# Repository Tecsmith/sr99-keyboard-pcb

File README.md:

# SR99-Keyboard-PCB

> :warning: **WIP:** Work in Progress design, and is not tested.  Please hold-off on building until the design can be verified and the software is written.

## Intent

A 980-layout (99-key) compact near-full size keyboard.

## Progression

> :bangbang: This is a "when I'm bored" project - so "significant" progress is not expected.

- **12 Jun 2026**
  - KiCAD 10 re-do done, but not built
- **15 Nov 2025**: Re-do begins!
  - EAGLE design abandoned in favour of KiCAD design
  - `STM32F411` discarded for **`STM32G474`**
- ~~**27 Sep 2024**: Beta 1 done~~
  - ~~:warning: Not manufactured~~
  - ~~:warning: Not tested~~
- See [CHANGELOG.md](CHANGELOG.md)

<!--
### Resources

 - Schematic PDF [here](docs/sr99-revXXX.pdf)
 - EAGLE BRD *(PCB)* [here](EAGLE/sr99/sr99-revXXX.brd)
 - EAGLE SCH *(Schematic)* [here](EAGLE/sr99/sr99-revXXX.sch)
-->

### Beta PCB renders

#### Top

#### Bottom *(Component side)*

◊
### Layout ideation renders

#### Render

#### Layout

#### Matrix coordinates *(QMK & VIA)*

## Planned Features

- [ ] QMK build, with Via/l support
- [x] 1x `STM32G474` STM32 CPU *(based on Black Pill design)*
- [x] 1x `M95640-DRE` 8K SPI EEPROM Module
- [x] 3x `MC74HC589A` SPI Input Shift Registers *- possibly faster scan rates*
- [x] 2x `IS31FL3743B` RGB Drivers, with independent LDOs
- [ ] 2x SKYLOONG rotary encoder/switch positions
- [x] UDB C-Series Usb-C JST-SH

<!--
#### Addons / Wishlist

- [ ] DIP Switch daughter board *(4-position)*
- [ ] ~~Case slide switch daughter board *(Win/Mac 2-state, + USB+BT+2.4GHz 3-state)*~~ *(To do)*
- [ ] USB 2.0 Hub
-->

<!--
## Wishlist

- [ ] Drop in replacement PCB *(e.g. compatible standoff positions)* for:
    - Brutal v2 1800
    - Monsgeek M2
    - ~~Skyloong GK980~~ *(The GK980 has a 0.5U gap between Esc and F1, making it not the same footprint as the B1k8 and M2.)*
-->

---

Made with :heart: by [**Silvino R**](https://github.com/silvinor)

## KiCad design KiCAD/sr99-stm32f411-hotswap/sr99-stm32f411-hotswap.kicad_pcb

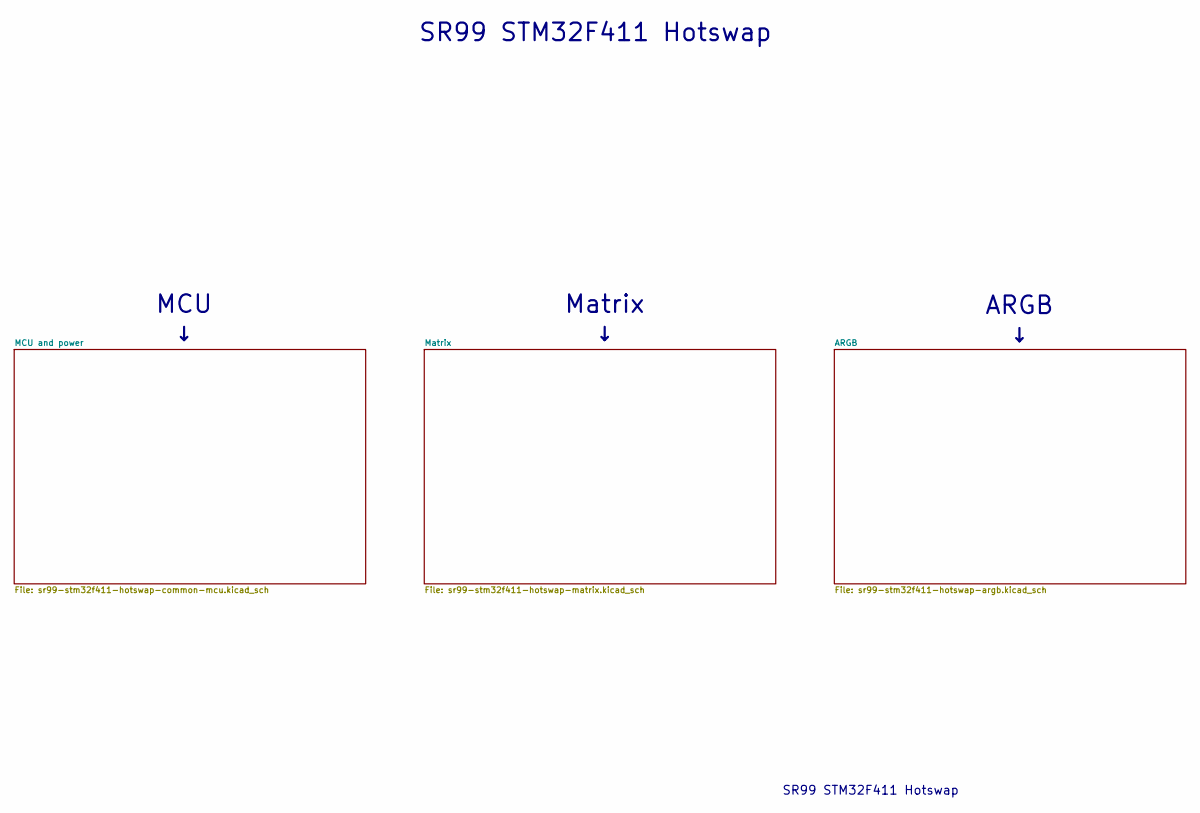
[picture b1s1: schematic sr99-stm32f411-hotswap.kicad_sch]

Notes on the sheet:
ARGB ↓
MCU ↓
SR99 STM32F411 Hotswap
Matrix ↓

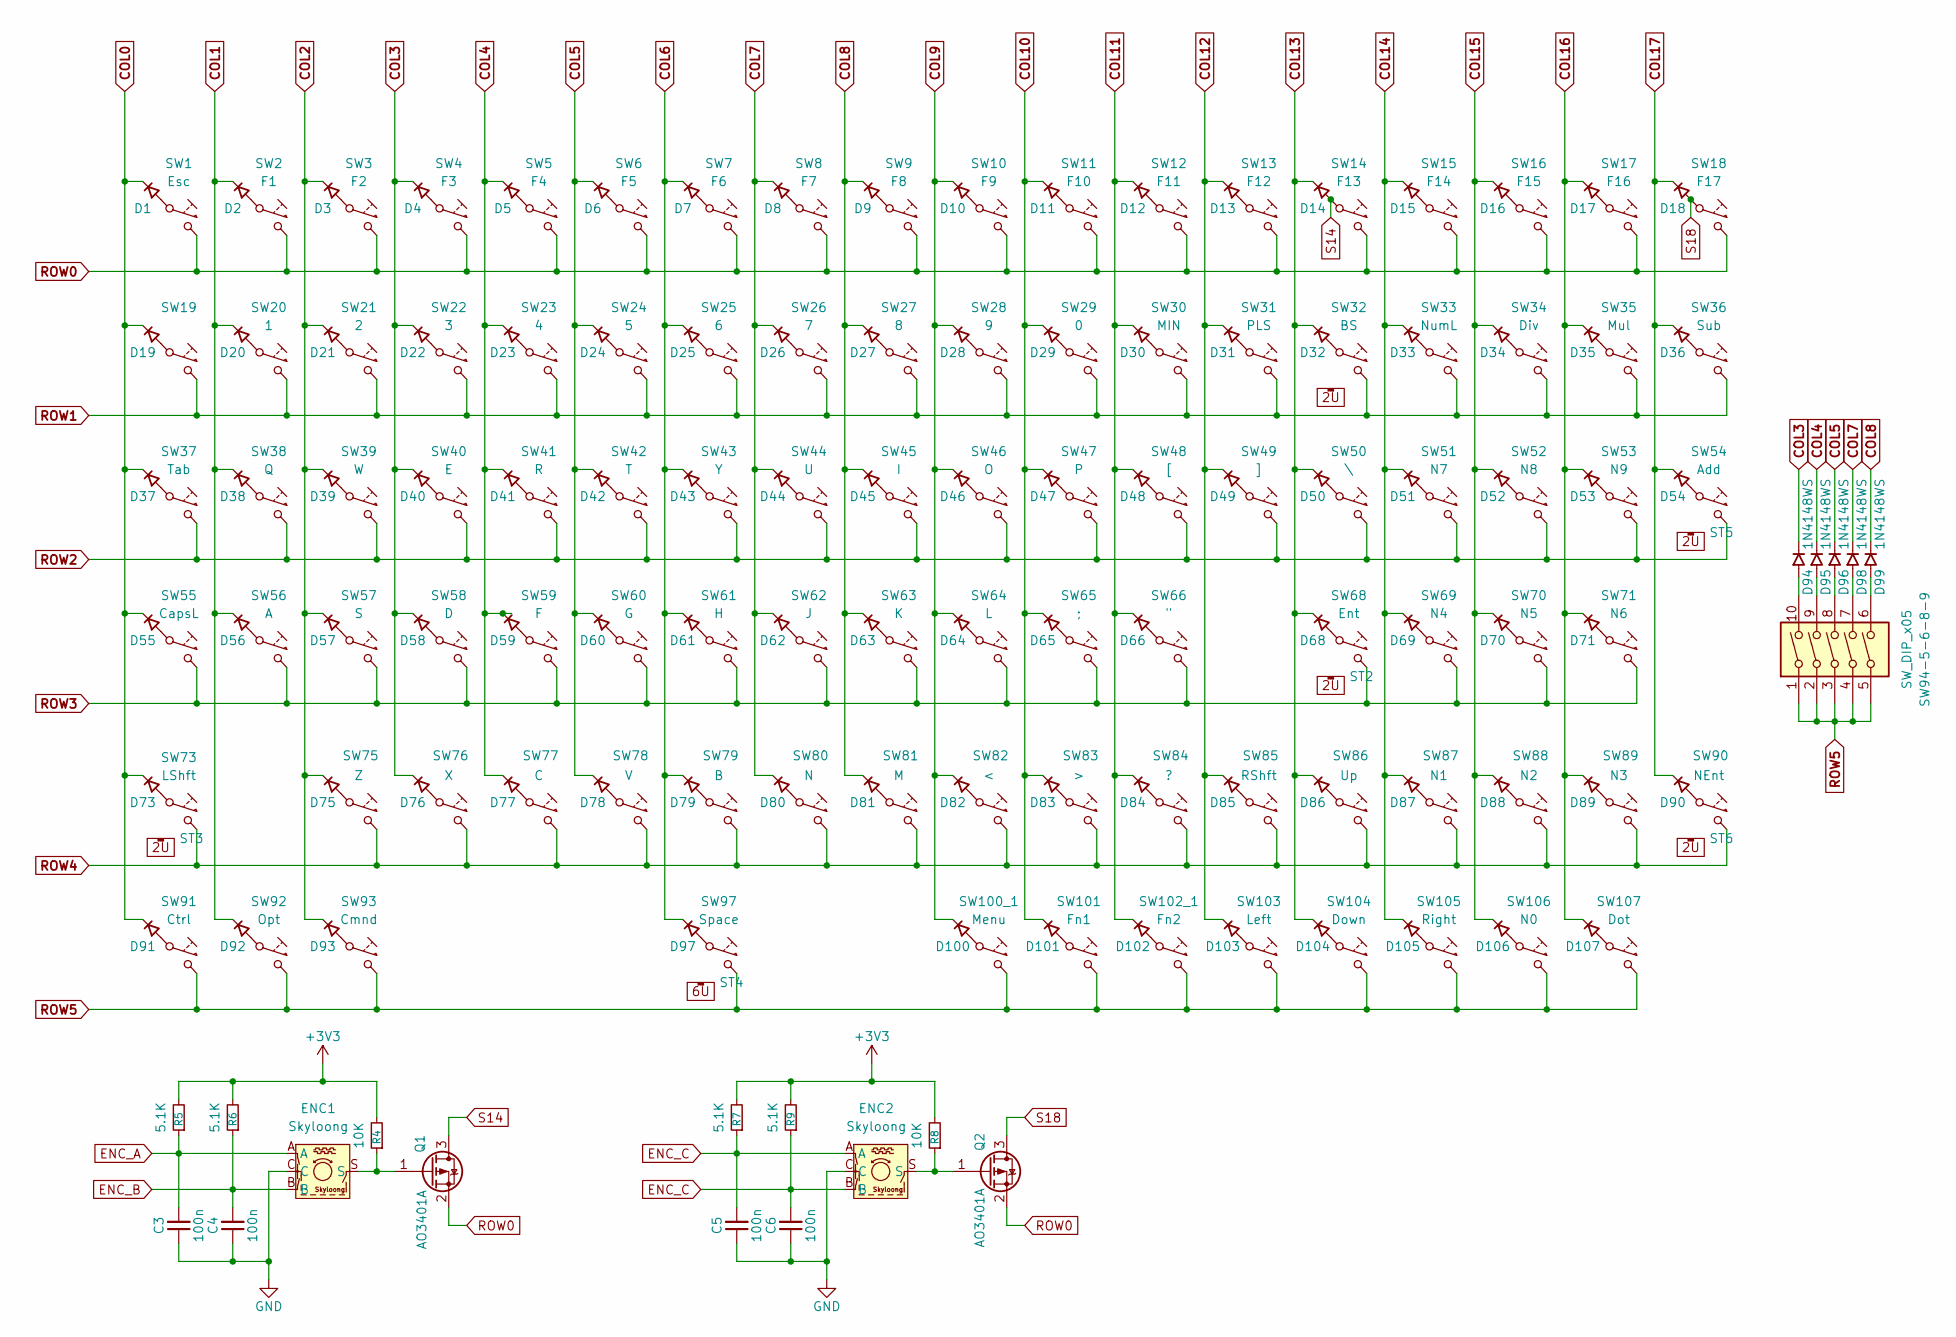
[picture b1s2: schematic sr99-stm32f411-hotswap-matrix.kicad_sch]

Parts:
C3, C4, C5, C6: 100n; C_0603_1608Metric_Pad1.08x0.95mm_HandSolder
D1, D2, D3, D4, D5, D6, D7, D8, D9, D10, D11, D12, D13, D14, D15, D16, D17, D18, D19, D20, D21, D22, D23, D24, D25, D26, D27, D28, D29, D30, D31, D32, D33, D34, D35, D36, D37, D38, D39, D40, D41, D42, D43, D44, D45, D46, D47, D48, D49, D50, D51, D52, D53, D54, D55, D56, D57, D58, D59, D60, D61, D62, D63, D64, D65, D66, D68, D69, D70, D71, D73, D75, D76, D77, D78, D79, D80, D81, D82, D83, D84, D85, D86, D87, D88, D89, D90, D91, D92, D93, D97, D100, D101, D102, D103, D104, D105, D106, D107: 1N4148WS; D_SOD-323_HandSoldering
D94, D95, D96, D98, D99: 1N4148WS
ENC1, ENC2: Skyloong; SW_Skyloong_Enc
Q1, Q2: AO3401A; SOT-23
R4, R8: 10K; R_0603_1608Metric_Pad0.98x0.95mm_HandSolder
R5, R6, R7, R9: 5.1K; R_0603_1608Metric_Pad0.98x0.95mm_HandSolder
ST1, ST2, ST3, ST5, ST6: STAB_2U
ST4: STAB_6U
SW1: Esc; SW_MX_HotSwap
SW2: F1; SW_MX_HotSwap
SW3: F2; SW_MX_HotSwap
SW4: F3; SW_MX_HotSwap
SW5: F4; SW_MX_HotSwap
SW6: F5; SW_MX_HotSwap
SW7: F6; SW_MX_HotSwap
SW8: F7; SW_MX_HotSwap
SW9: F8; SW_MX_HotSwap
SW10: F9; SW_MX_HotSwap
SW11: F10; SW_MX_HotSwap
SW12: F11; SW_MX_HotSwap
SW13: F12; SW_MX_HotSwap
SW14: F13; SW_MX_HotSwap
SW15: F14; SW_MX_HotSwap
SW16: F15; SW_MX_HotSwap
SW17: F16; SW_MX_HotSwap
SW18: F17; SW_MX_HotSwap
SW19: SW_MX_HotSwap
SW20: 1; SW_MX_HotSwap
SW21: 2; SW_MX_HotSwap
SW22: 3; SW_MX_HotSwap
SW23: 4; SW_MX_HotSwap
SW24: 5; SW_MX_HotSwap
SW25: 6; SW_MX_HotSwap
SW26: 7; SW_MX_HotSwap
SW27: 8; SW_MX_HotSwap
SW28: 9; SW_MX_HotSwap
SW29: 0; SW_MX_HotSwap
SW30: MIN; SW_MX_HotSwap
SW31: PLS; SW_MX_HotSwap
SW32: BS; SW_MX_HotSwap
SW33: NumL; SW_MX_HotSwap
SW34: Div; SW_MX_HotSwap
SW35: Mul; SW_MX_HotSwap
SW36: Sub; SW_MX_HotSwap
SW37: Tab; SW_MX_HotSwap
SW38: Q; SW_MX_HotSwap
SW39: W; SW_MX_HotSwap
SW40: E; SW_MX_HotSwap
SW41: R; SW_MX_HotSwap
SW42: T; SW_MX_HotSwap
SW43: Y; SW_MX_HotSwap
SW44: U; SW_MX_HotSwap
SW45: I; SW_MX_HotSwap
SW46: O; SW_MX_HotSwap
SW47: P; SW_MX_HotSwap
SW48: [; SW_MX_HotSwap
SW49: ]; SW_MX_HotSwap
SW50: \; SW_MX_HotSwap
SW51: N7; SW_MX_HotSwap
SW52: N8; SW_MX_HotSwap
SW53: N9; SW_MX_HotSwap
SW54: Add; SW_MX_HotSwap
SW55: CapsL; SW_MX_HotSwap
SW56: A; SW_MX_HotSwap
SW57: S; SW_MX_HotSwap
SW58: D; SW_MX_HotSwap
SW59: F; SW_MX_HotSwap
SW60: G; SW_MX_HotSwap
SW61: H; SW_MX_HotSwap
SW62: J; SW_MX_HotSwap
SW63: K; SW_MX_HotSwap
SW64: L; SW_MX_HotSwap
SW65: ;; SW_MX_HotSwap
SW66: "; SW_MX_HotSwap
SW68: Ent; SW_MX_HotSwap
SW69: N4; SW_MX_HotSwap
SW70: N5; SW_MX_HotSwap
SW71: N6; SW_MX_HotSwap
SW73: LShft; SW_MX_HotSwap
SW75: Z; SW_MX_HotSwap
SW76: X; SW_MX_HotSwap
SW77: C; SW_MX_HotSwap
SW78: V; SW_MX_HotSwap
SW79: B; SW_MX_HotSwap
SW80: N; SW_MX_HotSwap
SW81: M; SW_MX_HotSwap
SW82: <; SW_MX_HotSwap
SW83: >; SW_MX_HotSwap
SW84: ?; SW_MX_HotSwap
SW85: RShft; SW_MX_HotSwap
SW86: Up; SW_MX_HotSwap
SW87: N1; SW_MX_HotSwap
SW88: N2; SW_MX_HotSwap
SW89: N3; SW_MX_HotSwap
SW90: NEnt; SW_MX_HotSwap
SW91: Ctrl; SW_MX_HotSwap
SW92: Opt; SW_MX_HotSwap
SW93: Cmnd; SW_MX_HotSwap
SW94-5-6-8-9: SW_DIP_x05
SW97: Space; SW_MX_HotSwap
SW100_1: Menu; SW_MX_HotSwap
SW101: Fn1; SW_MX_HotSwap
SW102_1: Fn2; SW_MX_HotSwap
SW103: Left; SW_MX_HotSwap
SW104: Down; SW_MX_HotSwap
SW105: Right; SW_MX_HotSwap
SW106: N0; SW_MX_HotSwap
SW107: Dot; SW_MX_HotSwap

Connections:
+3V3: R4.2, R5.2, R6.2, R7.2, R8.2, R9.2
COL0: D1.1 (K), D19.1 (K), D37.1 (K), D55.1 (K), D73.1 (K), D91.1 (K)
COL1: D2.1 (K), D20.1 (K), D38.1 (K), D56.1 (K), D92.1 (K)
COL2: D3.1 (K), D21.1 (K), D39.1 (K), D57.1 (K), D75.1 (K), D93.1 (K)
COL3: D4.1 (K), D22.1 (K), D40.1 (K), D58.1 (K), D76.1 (K), D94.1 (K)
COL4: D5.1 (K), D23.1 (K), D41.1 (K), D59.1 (K), D77.1 (K), D95.1 (K)
COL5: D6.1 (K), D24.1 (K), D42.1 (K), D60.1 (K), D78.1 (K), D96.1 (K)
COL6: D7.1 (K), D25.1 (K), D43.1 (K), D61.1 (K), D79.1 (K), D97.1 (K)
COL7: D8.1 (K), D26.1 (K), D44.1 (K), D62.1 (K), D80.1 (K), D98.1 (K)
COL8: D9.1 (K), D27.1 (K), D45.1 (K), D63.1 (K), D81.1 (K), D99.1 (K)
COL9: D10.1 (K), D28.1 (K), D46.1 (K), D64.1 (K), D82.1 (K), D100.1 (K)
COL10: D11.1 (K), D29.1 (K), D47.1 (K), D65.1 (K), D83.1 (K), D101.1 (K)
COL11: D12.1 (K), D30.1 (K), D48.1 (K), D66.1 (K), D84.1 (K), D102.1 (K)
COL12: D13.1 (K), D31.1 (K), D49.1 (K), D85.1 (K), D103.1 (K)
COL13: D14.1 (K), D32.1 (K), D50.1 (K), D68.1 (K), D86.1 (K), D104.1 (K)
COL14: D15.1 (K), D33.1 (K), D51.1 (K), D69.1 (K), D87.1 (K), D105.1 (K)
COL15: D16.1 (K), D34.1 (K), D52.1 (K), D70.1 (K), D88.1 (K), D106.1 (K)
COL16: D17.1 (K), D35.1 (K), D53.1 (K), D71.1 (K), D89.1 (K), D107.1 (K)
COL17: D18.1 (K), D36.1 (K), D54.1 (K), D90.1 (K)
ENC_A: C3.2, ENC1.A, R5.1
ENC_B: C4.2, ENC1.B, R6.1
ENC_C: C5.2, C6.2, ENC2.A, ENC2.B, R7.1, R9.1
GND: C3.1, C4.1, C5.1, C6.1, ENC1.C, ENC2.C; also elsewhere on the board
unnamed: D1.2 (A), SW1.1
unnamed: D2.2 (A), SW2.1
unnamed: D3.2 (A), SW3.1
unnamed: D4.2 (A), SW4.1
unnamed: D5.2 (A), SW5.1
unnamed: D6.2 (A), SW6.1
unnamed: D7.2 (A), SW7.1
unnamed: D8.2 (A), SW8.1
unnamed: D9.2 (A), SW9.1
unnamed: D10.2 (A), SW10.1
unnamed: D11.2 (A), SW11.1
unnamed: D12.2 (A), SW12.1
unnamed: D13.2 (A), SW13.1
unnamed: D15.2 (A), SW15.1
unnamed: D16.2 (A), SW16.1
unnamed: D17.2 (A), SW17.1
unnamed: D19.2 (A), SW19.1
unnamed: D20.2 (A), SW20.1
unnamed: D21.2 (A), SW21.1
unnamed: D22.2 (A), SW22.1
unnamed: D23.2 (A), SW23.1
unnamed: D24.2 (A), SW24.1
unnamed: D25.2 (A), SW25.1
unnamed: D26.2 (A), SW26.1
unnamed: D27.2 (A), SW27.1
unnamed: D28.2 (A), SW28.1
unnamed: D29.2 (A), SW29.1
unnamed: D30.2 (A), SW30.1
unnamed: D31.2 (A), SW31.1
unnamed: D32.2 (A), SW32.1
unnamed: D33.2 (A), SW33.1
unnamed: D34.2 (A), SW34.1
unnamed: D35.2 (A), SW35.1
unnamed: D36.2 (A), SW36.1
unnamed: D37.2 (A), SW37.1
unnamed: D38.2 (A), SW38.1
unnamed: D39.2 (A), SW39.1
unnamed: D40.2 (A), SW40.1
unnamed: D41.2 (A), SW41.1
unnamed: D42.2 (A), SW42.1
unnamed: D43.2 (A), SW43.1
unnamed: D44.2 (A), SW44.1
unnamed: D45.2 (A), SW45.1
unnamed: D46.2 (A), SW46.1
unnamed: D47.2 (A), SW47.1
unnamed: D48.2 (A), SW48.1
unnamed: D49.2 (A), SW49.1
unnamed: D50.2 (A), SW50.1
unnamed: D51.2 (A), SW51.1
unnamed: D52.2 (A), SW52.1
unnamed: D53.2 (A), SW53.1
unnamed: D54.2 (A), SW54.1
unnamed: D55.2 (A), SW55.1
unnamed: D56.2 (A), SW56.1
unnamed: D57.2 (A), SW57.1
unnamed: D58.2 (A), SW58.1
unnamed: D59.2 (A), SW59.1
unnamed: D60.2 (A), SW60.1
unnamed: D61.2 (A), SW61.1
unnamed: D62.2 (A), SW62.1
unnamed: D63.2 (A), SW63.1
unnamed: D64.2 (A), SW64.1
unnamed: D65.2 (A), SW65.1
unnamed: D66.2 (A), SW66.1
unnamed: D68.2 (A), SW68.1
unnamed: D69.2 (A), SW69.1
unnamed: D70.2 (A), SW70.1
unnamed: D71.2 (A), SW71.1
unnamed: D73.2 (A), SW73.1
unnamed: D75.2 (A), SW75.1
unnamed: D76.2 (A), SW76.1
unnamed: D77.2 (A), SW77.1
unnamed: D78.2 (A), SW78.1
unnamed: D79.2 (A), SW79.1
unnamed: D80.2 (A), SW80.1
unnamed: D81.2 (A), SW81.1
unnamed: D82.2 (A), SW82.1
unnamed: D83.2 (A), SW83.1
unnamed: D84.2 (A), SW84.1
unnamed: D85.2 (A), SW85.1
unnamed: D86.2 (A), SW86.1
unnamed: D87.2 (A), SW87.1
unnamed: D88.2 (A), SW88.1
unnamed: D89.2 (A), SW89.1
unnamed: D90.2 (A), SW90.1
unnamed: D91.2 (A), SW91.1
unnamed: D92.2 (A), SW92.1
unnamed: D93.2 (A), SW93.1
unnamed: D94.2 (A), SW94-5-6-8-9.10
unnamed: D95.2 (A), SW94-5-6-8-9.9
unnamed: D96.2 (A), SW94-5-6-8-9.8
unnamed: D97.2 (A), SW97.1
unnamed: D98.2 (A), SW94-5-6-8-9.7
unnamed: D99.2 (A), SW94-5-6-8-9.6
unnamed: D100.2 (A), SW100_1.1
unnamed: D101.2 (A), SW101.1
unnamed: D102.2 (A), SW102_1.1
unnamed: D103.2 (A), SW103.1
unnamed: D104.2 (A), SW104.1
unnamed: D105.2 (A), SW105.1
unnamed: D106.2 (A), SW106.1
unnamed: D107.2 (A), SW107.1
unnamed: ENC1.S, Q1.1 (G), R4.1
unnamed: ENC2.S, Q2.1 (G), R8.1
ROW0: Q1.2 (S), Q2.2 (S), SW1.2, SW2.2, SW3.2, SW4.2, SW5.2, SW6.2, SW7.2, SW8.2, SW9.2, SW10.2, SW11.2, SW12.2, SW13.2, SW14.2, SW15.2, SW16.2, SW17.2, SW18.2
ROW1: SW19.2, SW20.2, SW21.2, SW22.2, SW23.2, SW24.2, SW25.2, SW26.2, SW27.2, SW28.2, SW29.2, SW30.2, SW31.2, SW32.2, SW33.2, SW34.2, SW35.2, SW36.2
ROW2: SW37.2, SW38.2, SW39.2, SW40.2, SW41.2, SW42.2, SW43.2, SW44.2, SW45.2, SW46.2, SW47.2, SW48.2, SW49.2, SW50.2, SW51.2, SW52.2, SW53.2, SW54.2
ROW3: SW55.2, SW56.2, SW57.2, SW58.2, SW59.2, SW60.2, SW61.2, SW62.2, SW63.2, SW64.2, SW65.2, SW66.2, SW68.2, SW69.2, SW70.2, SW71.2
ROW4: SW73.2, SW75.2, SW76.2, SW77.2, SW78.2, SW79.2, SW80.2, SW81.2, SW82.2, SW83.2, SW84.2, SW85.2, SW86.2, SW87.2, SW88.2, SW89.2, SW90.2
ROW5: SW91.2, SW92.2, SW93.2, SW94-5-6-8-9.1, SW94-5-6-8-9.2, SW94-5-6-8-9.3, SW94-5-6-8-9.4, SW94-5-6-8-9.5, SW97.2, SW100_1.2, SW101.2, SW102_1.2, SW103.2, SW104.2, SW105.2, SW106.2, SW107.2
S14: D14.2 (A), Q1.3 (D), SW14.1
S18: D18.2 (A), Q2.3 (D), SW18.1

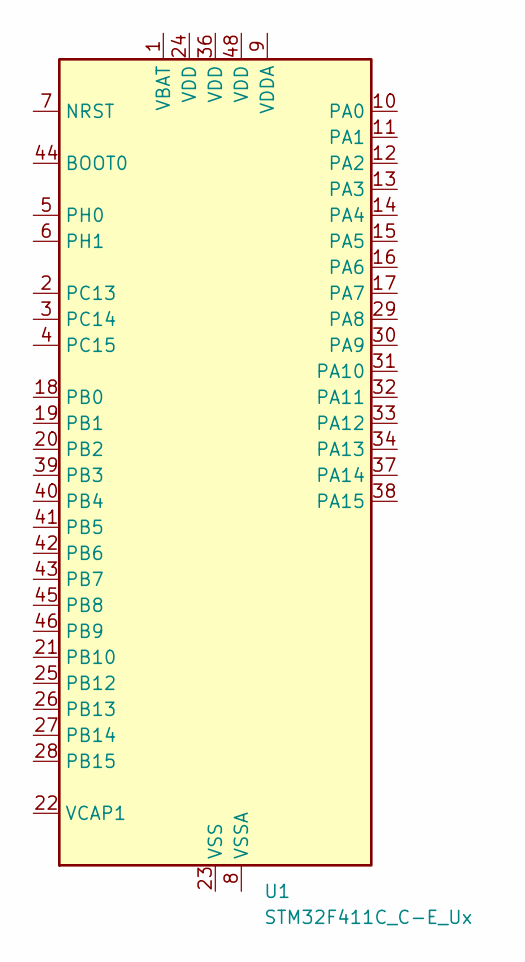
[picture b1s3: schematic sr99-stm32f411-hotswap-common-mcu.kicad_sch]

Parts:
U1: STM32F411C_C-E_Ux; QFN-48-1EP_7x7mm_P0.5mm_EP5.6x5.6mm

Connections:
unnamed: U1.23 (VSS), U1.35 (VSS), U1.47 (VSS), U1.49 (VSS)

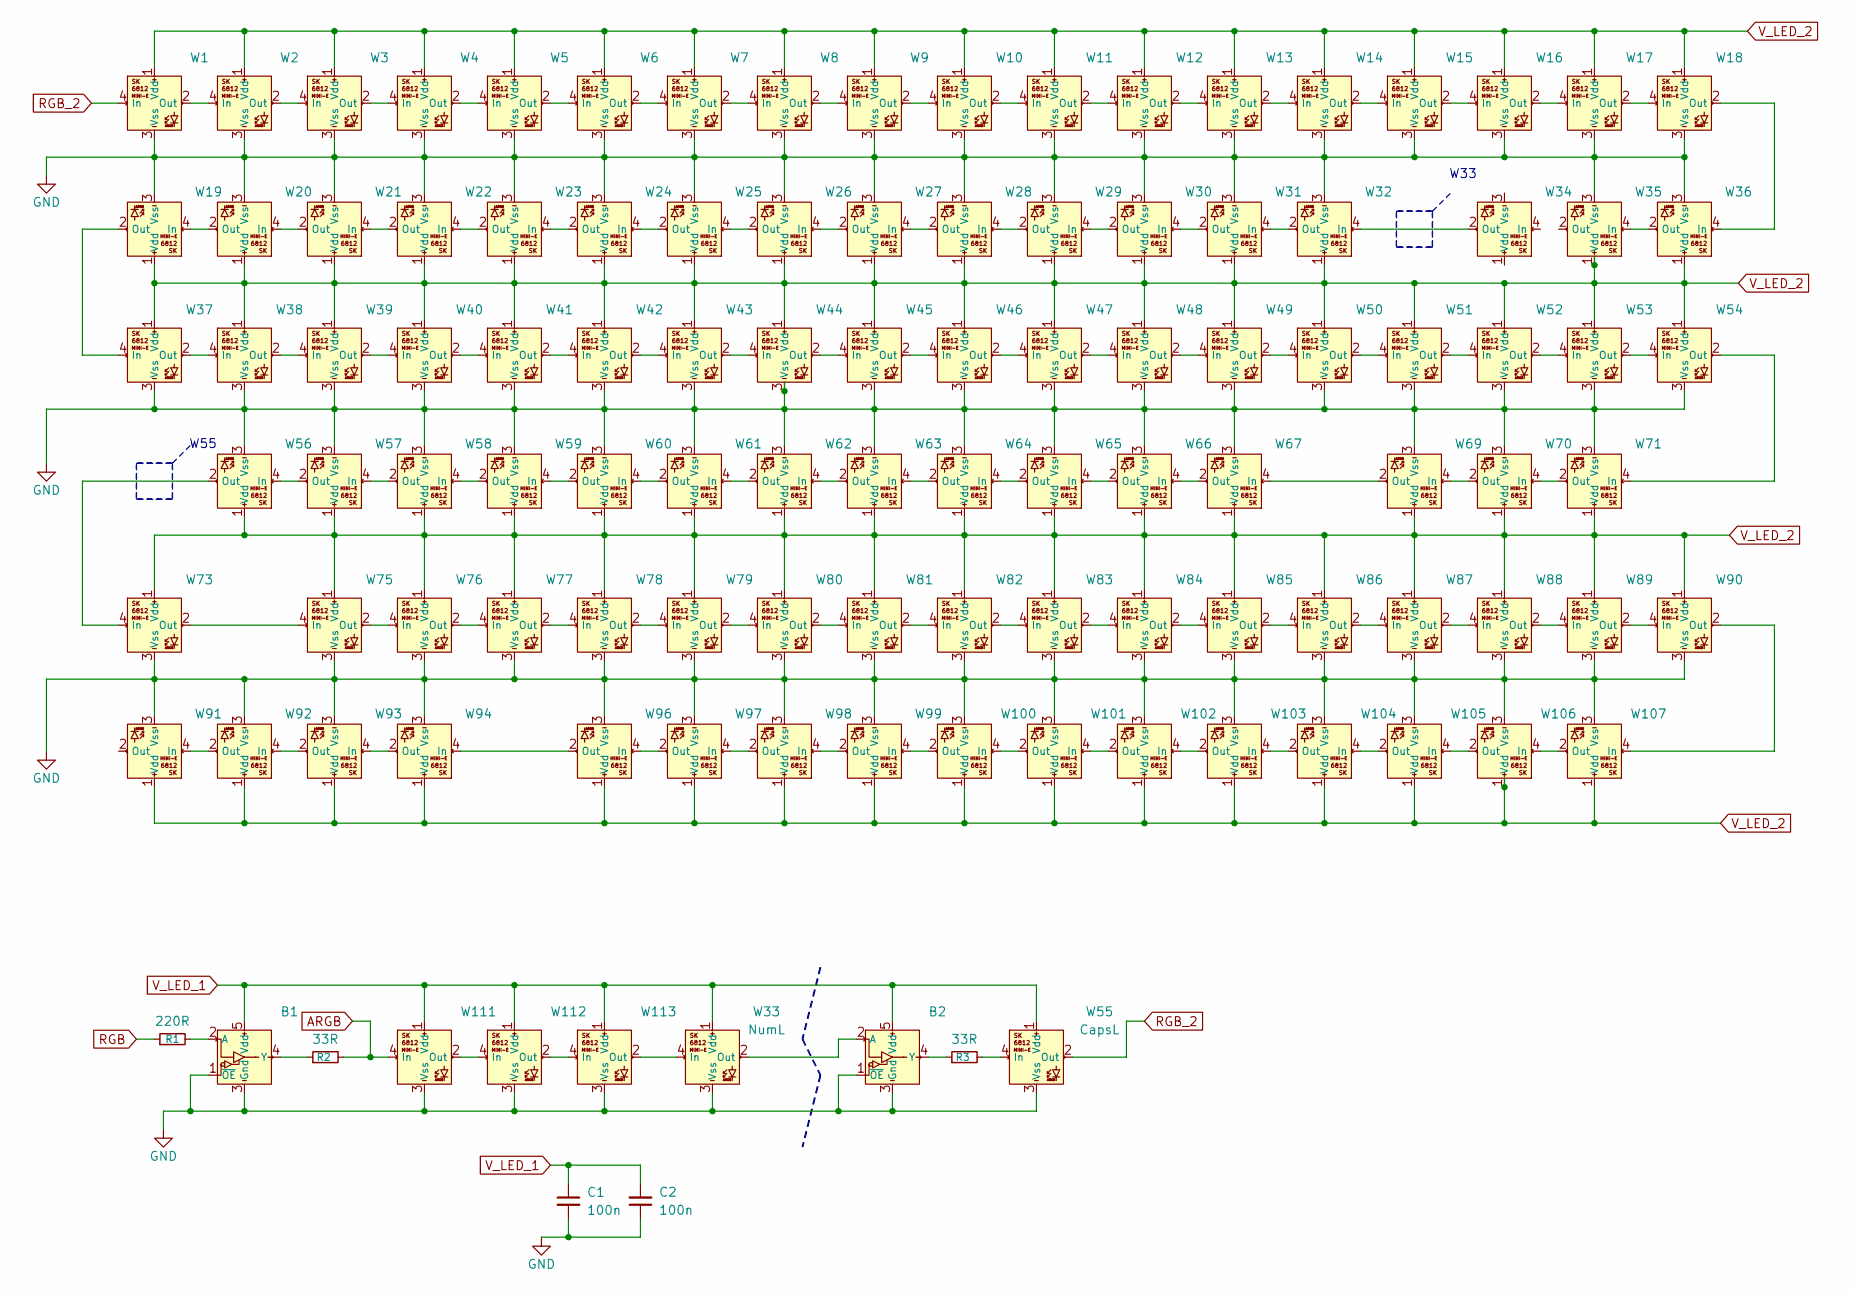
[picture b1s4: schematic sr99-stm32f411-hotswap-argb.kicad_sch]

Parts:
B1, B2: SOT-23-5
C1, C2: 100n; C_0603_1608Metric_Pad1.08x0.95mm_HandSolder
R1: 220R; R_0603_1608Metric_Pad0.98x0.95mm_HandSolder
R2, R3: 33R; R_0603_1608Metric_Pad0.98x0.95mm_HandSolder
W1, W2, W3, W4, W5, W6, W7, W8, W9, W10, W11, W12, W13, W14, W15, W16, W17, W18, W19, W20, W21, W22, W23, W24, W25, W26, W27, W28, W29, W30, W31, W32, W34, W35, W36, W37, W38, W39, W40, W41, W42, W43, W44, W45, W46, W47, W48, W49, W50, W51, W52, W53, W54, W56, W57, W58, W59, W60, W61, W62, W63, W64, W65, W66, W67, W69, W70, W71, W73, W75, W76, W77, W78, W79, W80, W81, W82, W83, W84, W85, W86, W87, W88, W89, W90, W91, W92, W93, W94, W96, W97, W98, W99, W100, W101, W102, W103, W104, W105, W106, W107, W111, W112, W113: SK6812MINI-E
W33: NumL; SK6812MINI-E
W55: CapsL; SK6812MINI-E

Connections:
ARGB: R2.2, W111.4 (In)
GND: B1.1 (~OE), B1.3 (Gnd), B2.1 (~OE), B2.3 (Gnd), C1.2, C2.1, W1.3 (Vss), W2.3 (Vss), W3.3 (Vss), W4.3 (Vss), W5.3 (Vss), W6.3 (Vss), W7.3 (Vss), W8.3 (Vss), W9.3 (Vss), W10.3 (Vss), W11.3 (Vss), W12.3 (Vss), W13.3 (Vss), W14.3 (Vss), W15.3 (Vss), W16.3 (Vss), W17.3 (Vss), W18.3 (Vss), W19.3 (Vss), W20.3 (Vss), W21.3 (Vss), W22.3 (Vss), W23.3 (Vss), W24.3 (Vss), W25.3 (Vss), W26.3 (Vss), W27.3 (Vss), W28.3 (Vss), W29.3 (Vss), W30.3 (Vss), W31.3 (Vss), W32.3 (Vss), W33.3 (Vss), W35.3 (Vss), W36.3 (Vss), W37.3 (Vss), W38.3 (Vss), W39.3 (Vss), W40.3 (Vss), W41.3 (Vss), W42.3 (Vss), W43.3 (Vss), W44.3 (Vss), W45.3 (Vss), W46.3 (Vss), W47.3 (Vss), W48.3 (Vss), W49.3 (Vss), W50.3 (Vss), W51.3 (Vss), W52.3 (Vss), W53.3 (Vss), W54.3 (Vss), W55.3 (Vss), W56.3 (Vss), W57.3 (Vss), W58.3 (Vss), W59.3 (Vss), W60.3 (Vss), W61.3 (Vss), W62.3 (Vss), W63.3 (Vss), W64.3 (Vss), W65.3 (Vss), W66.3 (Vss), W67.3 (Vss), W69.3 (Vss), W70.3 (Vss), W71.3 (Vss), W73.3 (Vss), W75.3 (Vss), W76.3 (Vss), W77.3 (Vss), W78.3 (Vss), W79.3 (Vss), W80.3 (Vss), W81.3 (Vss), W82.3 (Vss), W83.3 (Vss), W84.3 (Vss), W85.3 (Vss), W86.3 (Vss), W87.3 (Vss), W88.3 (Vss), W89.3 (Vss), W90.3 (Vss), W91.3 (Vss), W92.3 (Vss), W93.3 (Vss), W94.3 (Vss), W96.3 (Vss), W97.3 (Vss), W98.3 (Vss), W99.3 (Vss), W100.3 (Vss), W101.3 (Vss), W102.3 (Vss), W103.3 (Vss), W104.3 (Vss), W105.3 (Vss), W106.3 (Vss), W107.3 (Vss), W111.3 (Vss), W112.3 (Vss), W113.3 (Vss); also elsewhere on the board
unnamed: B1.2 (A), R1.2
unnamed: B1.4 (Y), R2.1
unnamed: B2.2 (A), W33.2 (Out)
unnamed: B2.4 (Y), R3.1
unnamed: W1.2 (Out), W2.4 (In)
unnamed: W2.2 (Out), W3.4 (In)
unnamed: W3.2 (Out), W4.4 (In)
unnamed: W4.2 (Out), W5.4 (In)
unnamed: W5.2 (Out), W6.4 (In)
unnamed: W6.2 (Out), W7.4 (In)
unnamed: W7.2 (Out), W8.4 (In)
unnamed: W8.2 (Out), W9.4 (In)
unnamed: W10.2 (Out), W11.4 (In)
unnamed: W9.2 (Out), W10.4 (In)
unnamed: W11.2 (Out), W12.4 (In)
unnamed: W12.2 (Out), W13.4 (In)
unnamed: W13.2 (Out), W14.4 (In)
unnamed: W14.2 (Out), W15.4 (In)
unnamed: W15.2 (Out), W16.4 (In)
unnamed: W16.2 (Out), W17.4 (In)
unnamed: W17.2 (Out), W18.4 (In)
unnamed: W18.2 (Out), W36.4 (In)
unnamed: W19.2 (Out), W37.4 (In)
unnamed: W19.4 (In), W20.2 (Out)
unnamed: W20.4 (In), W21.2 (Out)
unnamed: W21.4 (In), W22.2 (Out)
unnamed: W22.4 (In), W23.2 (Out)
unnamed: W23.4 (In), W24.2 (Out)
unnamed: W24.4 (In), W25.2 (Out)
unnamed: W25.4 (In), W26.2 (Out)
unnamed: W26.4 (In), W27.2 (Out)
unnamed: W27.4 (In), W28.2 (Out)
unnamed: W28.4 (In), W29.2 (Out)
unnamed: W29.4 (In), W30.2 (Out)
unnamed: W30.4 (In), W31.2 (Out)
unnamed: W31.4 (In), W32.2 (Out)
unnamed: W32.4 (In), W34.2 (Out)
unnamed: W35.4 (In), W36.2 (Out)
unnamed: W37.2 (Out), W38.4 (In)
unnamed: W38.2 (Out), W39.4 (In)
unnamed: W39.2 (Out), W40.4 (In)
unnamed: W40.2 (Out), W41.4 (In)
unnamed: W41.2 (Out), W42.4 (In)
unnamed: W42.2 (Out), W43.4 (In)
unnamed: W43.2 (Out), W44.4 (In)
unnamed: W44.2 (Out), W45.4 (In)
unnamed: W45.2 (Out), W46.4 (In)
unnamed: W46.2 (Out), W47.4 (In)
unnamed: W47.2 (Out), W48.4 (In)
unnamed: W48.2 (Out), W49.4 (In)
unnamed: W49.2 (Out), W50.4 (In)
unnamed: W50.2 (Out), W51.4 (In)
unnamed: W51.2 (Out), W52.4 (In)
unnamed: W52.2 (Out), W53.4 (In)
unnamed: W53.2 (Out), W54.4 (In)
unnamed: W54.2 (Out), W71.4 (In)
unnamed: R3.2, W55.4 (In)
unnamed: W56.2 (Out), W73.4 (In)
unnamed: W56.4 (In), W57.2 (Out)
unnamed: W57.4 (In), W58.2 (Out)
unnamed: W58.4 (In), W59.2 (Out)
unnamed: W59.4 (In), W60.2 (Out)
unnamed: W60.4 (In), W61.2 (Out)
unnamed: W61.4 (In), W62.2 (Out)
unnamed: W62.4 (In), W63.2 (Out)
unnamed: W63.4 (In), W64.2 (Out)
unnamed: W64.4 (In), W65.2 (Out)
unnamed: W65.4 (In), W66.2 (Out)
unnamed: W66.4 (In), W67.2 (Out)
unnamed: W67.4 (In), W69.2 (Out)
unnamed: W69.4 (In), W70.2 (Out)
unnamed: W70.4 (In), W71.2 (Out)
unnamed 203: W73.2 (Out), W75.4 (In); also elsewhere on the board
unnamed: W75.2 (Out), W76.4 (In)
unnamed: W76.2 (Out), W77.4 (In)
unnamed: W77.2 (Out), W78.4 (In)
unnamed: W78.2 (Out), W79.4 (In)
unnamed: W79.2 (Out), W80.4 (In)
unnamed: W80.2 (Out), W81.4 (In)
unnamed: W81.2 (Out), W82.4 (In)
unnamed: W82.2 (Out), W83.4 (In)
unnamed: W83.2 (Out), W84.4 (In)
unnamed: W84.2 (Out), W85.4 (In)
unnamed: W85.2 (Out), W86.4 (In)
unnamed: W86.2 (Out), W87.4 (In)
unnamed: W87.2 (Out), W88.4 (In)
unnamed: W88.2 (Out), W89.4 (In)
unnamed: W89.2 (Out), W90.4 (In)
unnamed: W91.4 (In), W92.2 (Out)
unnamed: W92.4 (In), W93.2 (Out)
unnamed: W93.4 (In), W94.2 (Out)
unnamed: W94.4 (In), W96.2 (Out)
unnamed: W96.4 (In), W97.2 (Out)
unnamed: W97.4 (In), W98.2 (Out)
unnamed: W98.4 (In), W99.2 (Out)
unnamed: W99.4 (In), W100.2 (Out)
unnamed: W100.4 (In), W101.2 (Out)
unnamed: W101.4 (In), W102.2 (Out)
unnamed: W102.4 (In), W103.2 (Out)
unnamed: W103.4 (In), W104.2 (Out)
unnamed: W104.4 (In), W105.2 (Out)
unnamed: W105.4 (In), W106.2 (Out)
unnamed: W106.4 (In), W107.2 (Out)
unnamed: W90.2 (Out), W107.4 (In)
unnamed: W111.2 (Out), W112.4 (In)
unnamed: W112.2 (Out), W113.4 (In)
unnamed: W33.4 (In), W113.2 (Out)
RGB: R1.1
RGB_2: W1.4 (In), W55.2 (Out)
V_LED_1: B1.5 (Vdd), B2.5 (Vdd), C1.1, C2.2, W33.1 (Vdd), W55.1 (Vdd), W111.1 (Vdd), W112.1 (Vdd), W113.1 (Vdd)
V_LED_2: W1.1 (Vdd), W2.1 (Vdd), W3.1 (Vdd), W4.1 (Vdd), W5.1 (Vdd), W6.1 (Vdd), W7.1 (Vdd), W8.1 (Vdd), W9.1 (Vdd), W10.1 (Vdd), W11.1 (Vdd), W12.1 (Vdd), W13.1 (Vdd), W14.1 (Vdd), W15.1 (Vdd), W16.1 (Vdd), W17.1 (Vdd), W18.1 (Vdd), W19.1 (Vdd), W20.1 (Vdd), W21.1 (Vdd), W22.1 (Vdd), W23.1 (Vdd), W24.1 (Vdd), W25.1 (Vdd), W26.1 (Vdd), W27.1 (Vdd), W28.1 (Vdd), W29.1 (Vdd), W30.1 (Vdd), W31.1 (Vdd), W32.1 (Vdd), W35.1 (Vdd), W36.1 (Vdd), W37.1 (Vdd), W38.1 (Vdd), W39.1 (Vdd), W40.1 (Vdd), W41.1 (Vdd), W42.1 (Vdd), W43.1 (Vdd), W44.1 (Vdd), W45.1 (Vdd), W46.1 (Vdd), W47.1 (Vdd), W48.1 (Vdd), W49.1 (Vdd), W50.1 (Vdd), W51.1 (Vdd), W52.1 (Vdd), W53.1 (Vdd), W54.1 (Vdd), W56.1 (Vdd), W57.1 (Vdd), W58.1 (Vdd), W59.1 (Vdd), W60.1 (Vdd), W61.1 (Vdd), W62.1 (Vdd), W63.1 (Vdd), W64.1 (Vdd), W65.1 (Vdd), W66.1 (Vdd), W67.1 (Vdd), W69.1 (Vdd), W70.1 (Vdd), W71.1 (Vdd), W73.1 (Vdd), W75.1 (Vdd), W76.1 (Vdd), W77.1 (Vdd), W78.1 (Vdd), W79.1 (Vdd), W80.1 (Vdd), W81.1 (Vdd), W82.1 (Vdd), W83.1 (Vdd), W84.1 (Vdd), W85.1 (Vdd), W86.1 (Vdd), W87.1 (Vdd), W88.1 (Vdd), W89.1 (Vdd), W90.1 (Vdd), W91.1 (Vdd), W92.1 (Vdd), W93.1 (Vdd), W94.1 (Vdd), W96.1 (Vdd), W97.1 (Vdd), W98.1 (Vdd), W99.1 (Vdd), W100.1 (Vdd), W101.1 (Vdd), W102.1 (Vdd), W103.1 (Vdd), W104.1 (Vdd), W105.1 (Vdd), W106.1 (Vdd), W107.1 (Vdd); also elsewhere on the board

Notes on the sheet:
W33
W55

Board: 2 copper layers, 334 parts (0 on the bottom side), 242 nets, no tracks yet.

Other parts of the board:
W68, W74: SK6812MINI-E

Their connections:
GND: W68.3 (Vss), W74.3 (Vss); also elsewhere on the board
unnamed 203: W74.4 (In); also elsewhere on the board
V_LED_2: W68.1 (Vdd), W74.1 (Vdd); also elsewhere on the board

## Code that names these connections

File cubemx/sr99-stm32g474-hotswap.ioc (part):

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Mcu.Name=STM32G474C(B-C-E)Tx
Mcu.Package=LQFP48
Mcu.UserName=STM32G474CBTx
PA0.Mode=SYS_WakeUp0
PA0.Signal=SYS_WKUP1
PA1.GPIOParameters=GPIO_Label
PA1.GPIO_Label=MATRIX_CS
PA1.Signal=GPIO_Output
PA11.Mode=Device
PA11.Signal=USB_DM
PA12.Mode=Device
PA12.Signal=USB_DP
PA13.Mode=Serial_Wire
PA13.Signal=SYS_JTMS-SWDIO
PA14.Mode=Serial_Wire
PA14.Signal=SYS_JTCK-SWCLK
PA15.Mode=I2C
PA15.Signal=I2C1_SCL
PA4.GPIOParameters=GPIO_Label
PA4.GPIO_Label=EEPROM_CS
PA4.Signal=GPXTI4
PA5.Mode=Full_Duplex_Master
PA5.Signal=SPI1_SCK
PA6.Mode=Full_Duplex_Master
PA6.Signal=SPI1_MISO
PA7.Mode=Full_Duplex_Master
PA7.Signal=SPI1_MOSI
PB0.GPIOParameters=GPIO_Label
PB0.GPIO_Label=LED2_CS
PB0.Signal=GPIO_Output
PB1.GPIOParameters=GPIO_Label
PB1.GPIO_Label=LED1_CS
PB1.Signal=GPIO_Output
PB10.GPIOParameters=GPIO_Label
PB10.GPIO_Label=ROW0
PB10.Signal=GPIO_Output
PB11.GPIOParameters=GPIO_Label
PB11.GPIO_Label=ROW1
PB11.Signal=GPIO_Output
PB12.GPIOParameters=GPIO_Label
PB12.GPIO_Label=ROW2
PB12.Signal=GPIO_Output
PB13.GPIOParameters=GPIO_Label
PB13.GPIO_Label=ROW3
PB13.Signal=GPIO_Output
PB14.GPIOParameters=GPIO_Label
PB14.GPIO_Label=ROW4
PB14.Signal=GPIO_Output
PB15.GPIOParameters=GPIO_Label
PB15.GPIO_Label=ROW5
PB15.Signal=GPIO_Output
PB2.GPIOParameters=GPIO_Label
PB2.GPIO_Label=LED_NL
PB2.Signal=GPIO_Output
PB3.Signal=SYS_JTDO-SWO
PB4.Mode=Sink_AllSignals
PB4.Signal=UCPD1_CC2
PB5.GPIOParameters=GPIO_Label
PB5.GPIO_Label=LED_CL
PB5.Signal=GPIO_Output
PB6.Mode=Sink_AllSignals
PB6.Signal=UCPD1_CC1
PB7.Mode=I2C
PB7.Signal=I2C1_SDA
PB8-BOOT0.GPIOParameters=GPIO_Label
PB8-BOOT0.GPIO_Label=BOOT0
PB8-BOOT0.Signal=GPIO_Input
PC13.GPIOParameters=GPIO_Label
PC13.GPIO_Label=LED_PWR_EN
PC13.Signal=GPIO_Output
PF0-OSC_IN.Mode=HSE-External-Oscillator
PF0-OSC_IN.Signal=RCC_OSC_IN
PF1-OSC_OUT.Mode=HSE-External-Oscillator
PF1-OSC_OUT.Signal=RCC_OSC_OUT
RCC.HSE_VALUE=8000000
RCC.SYSCLKFreq_VALUE=16000000
board=custom

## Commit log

2022-10-31 intent uploaded
2023-02-14 Added 1800 variant
2023-03-24 initial sch
2023-03-25 docs
2023-03-26 added LED matrix
2023-03-26 led matrix done
2023-03-27 more docs
2023-03-30 move to ISP LED driver
2023-03-30 update to docs
2023-05-19 parking the north variant for now
2023-05-19 add the south variant
2024-09-23 update to docs, images
2024-09-24 pre- GND routing save
2024-09-24 post GND-routing save
2024-09-26 DIP Switch DB
2024-09-26 Beta 1
2024-09-27 Added "ground to boot" function
2024-09-28 Self-criticism
2024-11-06 confirmed m2 mounting points
2025-11-15 Remove EAGLE files & update docs
2025-11-15 wip-2025-11-15
2025-11-17 wip-2025-11-17
2025-11-19 FIle rename
2025-11-19 Docs cleanup
2025-11-19 wip-2025-11-19
2025-11-20 update-2025-11-20
2025-11-24 wip-2025-11-23
2026-06-10 pre-DRC upload
2026-06-11 ready to order
2026-06-11 removed stepped caps-lock
2026-06-15 Added Tag-Connect EC-06
2026-06-18 move folder
2026-06-21 updated some kb footprints
